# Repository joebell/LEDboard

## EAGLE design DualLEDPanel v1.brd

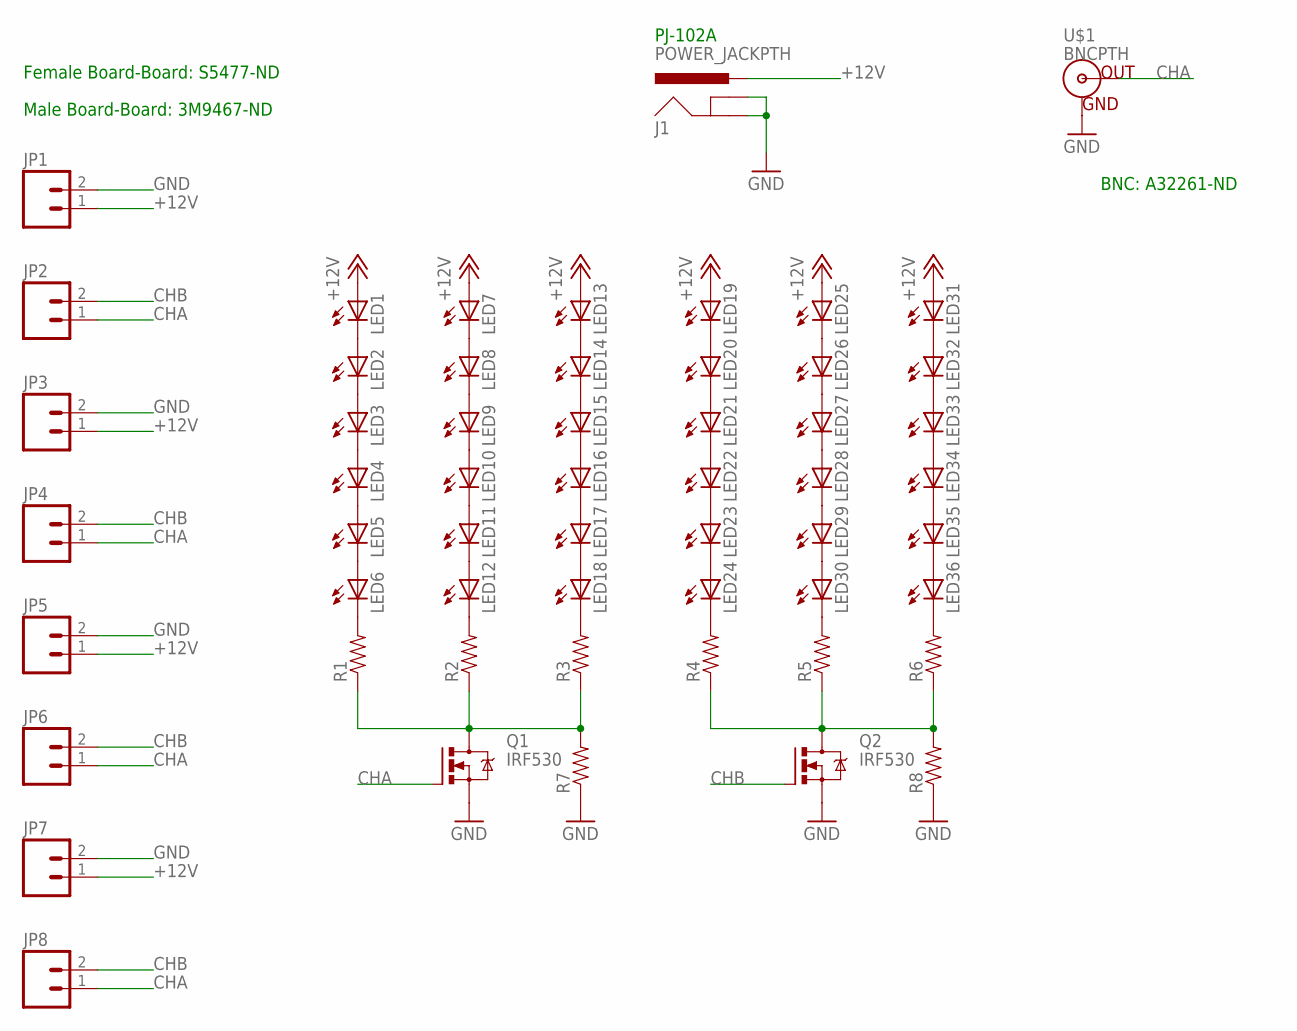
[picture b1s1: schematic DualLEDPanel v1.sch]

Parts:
J1: POWER_JACKPTH; POWER_JACK_PTH
JP1, JP2, JP3, JP4, JP5, JP6, JP7, JP8: M02PTH; 1X02
LED1, LED2, LED3, LED4, LED5, LED6, LED7, LED8, LED9, LED10, LED11, LED12, LED13, LED14, LED15, LED16, LED17, LED18, LED19, LED20, LED21, LED22, LED23, LED24, LED25, LED26, LED27, LED28, LED29, LED30, LED31, LED32, LED33, LED34, LED35, LED36: LED5MM
Q1, Q2: IRF530; TO220BV
R1, R2, R3, R4, R5, R6, R7, R8: RESISTORPTH-1/4W; AXIAL-0.4
U$1: BNCPTH; BNC

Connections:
+12V: J1.PWR, JP1.1, JP3.1, JP5.1, JP7.1, LED1.A, LED7.A, LED13.A, LED19.A, LED25.A, LED31.A
CHA: JP2.1, JP4.1, JP6.1, JP8.1, Q1.G, U$1.S (OUT)
CHB: JP2.2, JP4.2, JP6.2, JP8.2, Q2.G
GND: J1.GND, J1.GNDBREAK, JP1.2, JP3.2, JP5.2, JP7.2, Q1.S, Q2.S, R7.P$1 (1), R8.P$1 (1), U$1.GND
unnamed: LED1.K (C), LED2.A
unnamed: LED2.K (C), LED3.A
unnamed: LED3.K (C), LED4.A
unnamed: LED4.K (C), LED5.A
unnamed: LED5.K (C), LED6.A
unnamed: LED6.K (C), R1.P$2 (2)
unnamed: LED7.K (C), LED8.A
unnamed: LED8.K (C), LED9.A
unnamed: LED9.K (C), LED10.A
unnamed: LED10.K (C), LED11.A
unnamed: LED11.K (C), LED12.A
unnamed: LED12.K (C), R2.P$2 (2)
unnamed: LED13.K (C), LED14.A
unnamed: LED14.K (C), LED15.A
unnamed: LED15.K (C), LED16.A
unnamed: LED16.K (C), LED17.A
unnamed: LED17.K (C), LED18.A
unnamed: LED18.K (C), R3.P$2 (2)
unnamed: LED19.K (C), LED20.A
unnamed: LED20.K (C), LED21.A
unnamed: Q1.D, R1.P$1 (1), R2.P$1 (1), R3.P$1 (1), R7.P$2 (2)
unnamed: LED21.K (C), LED22.A
unnamed: LED22.K (C), LED23.A
unnamed: Q2.D, R4.P$1 (1), R5.P$1 (1), R6.P$1 (1), R8.P$2 (2)
unnamed: LED23.K (C), LED24.A
unnamed: LED24.K (C), R4.P$2 (2)
unnamed: LED25.K (C), LED26.A
unnamed: LED26.K (C), LED27.A
unnamed: LED27.K (C), LED28.A
unnamed: LED28.K (C), LED29.A
unnamed: LED29.K (C), LED30.A
unnamed: LED30.K (C), R5.P$2 (2)
unnamed: LED31.K (C), LED32.A
unnamed: LED32.K (C), LED33.A
unnamed: LED33.K (C), LED34.A
unnamed: LED34.K (C), LED35.A
unnamed: LED35.K (C), LED36.A
unnamed: LED36.K (C), R6.P$2 (2)

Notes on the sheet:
Female Board-Board: S5477-ND
Male Board-Board: 3M9467-ND
BNC: A32261-ND
PJ-102A

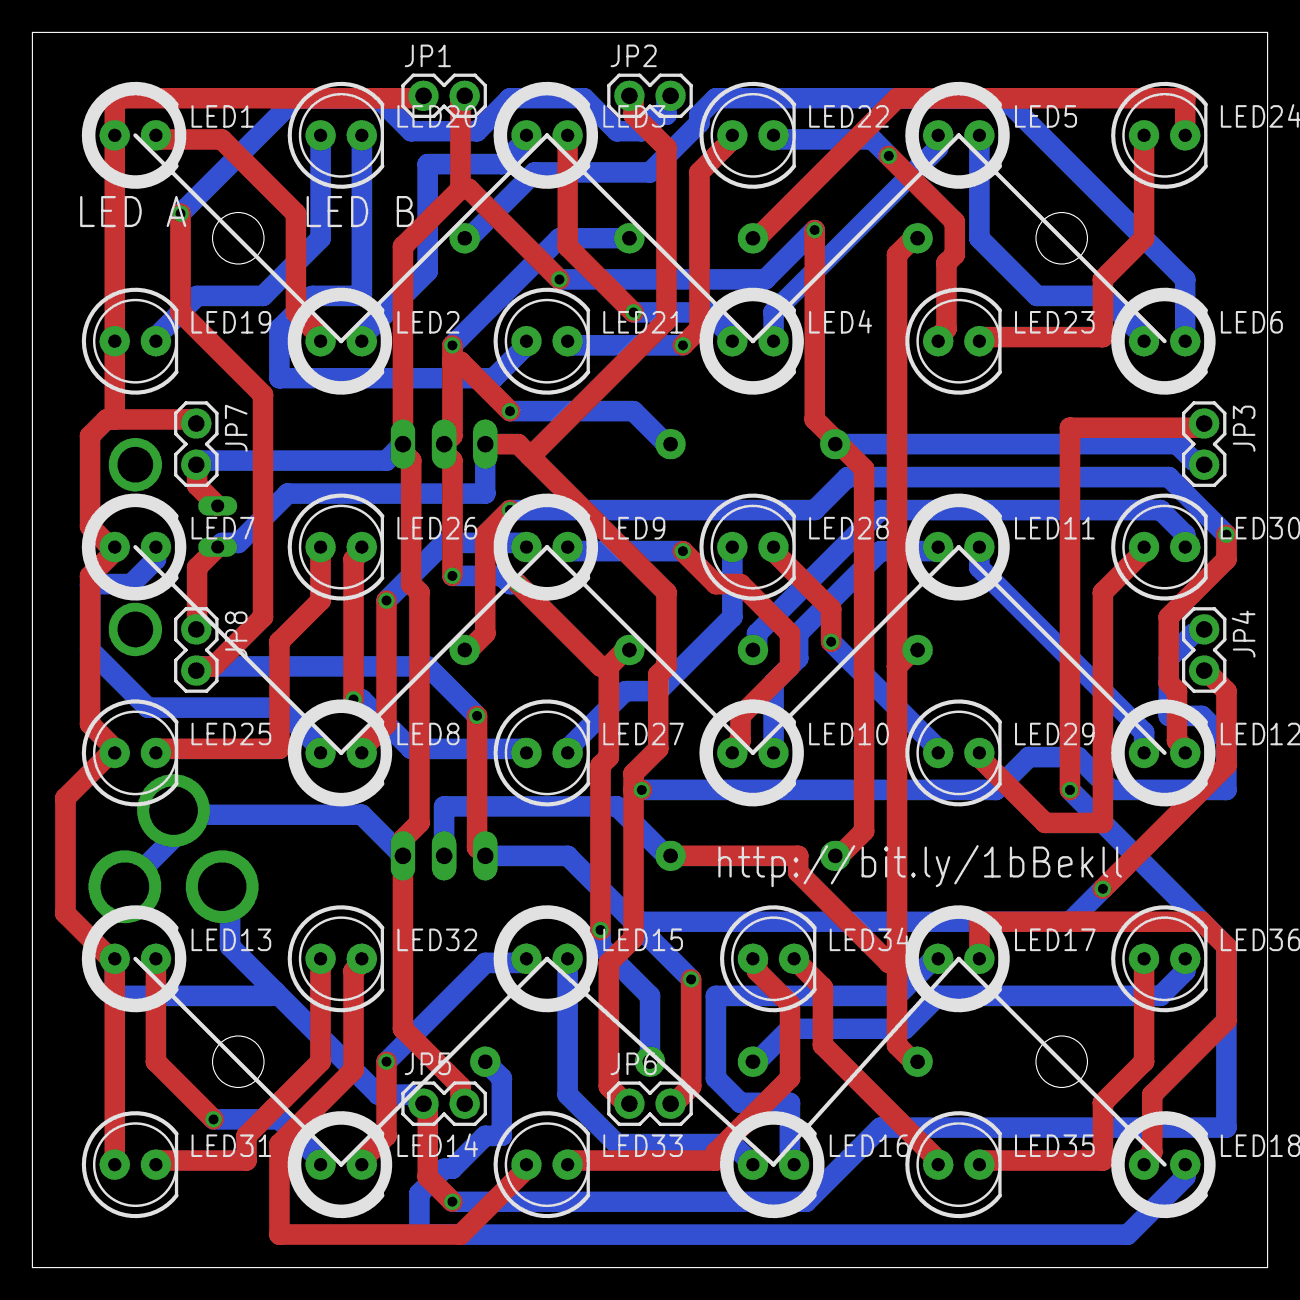
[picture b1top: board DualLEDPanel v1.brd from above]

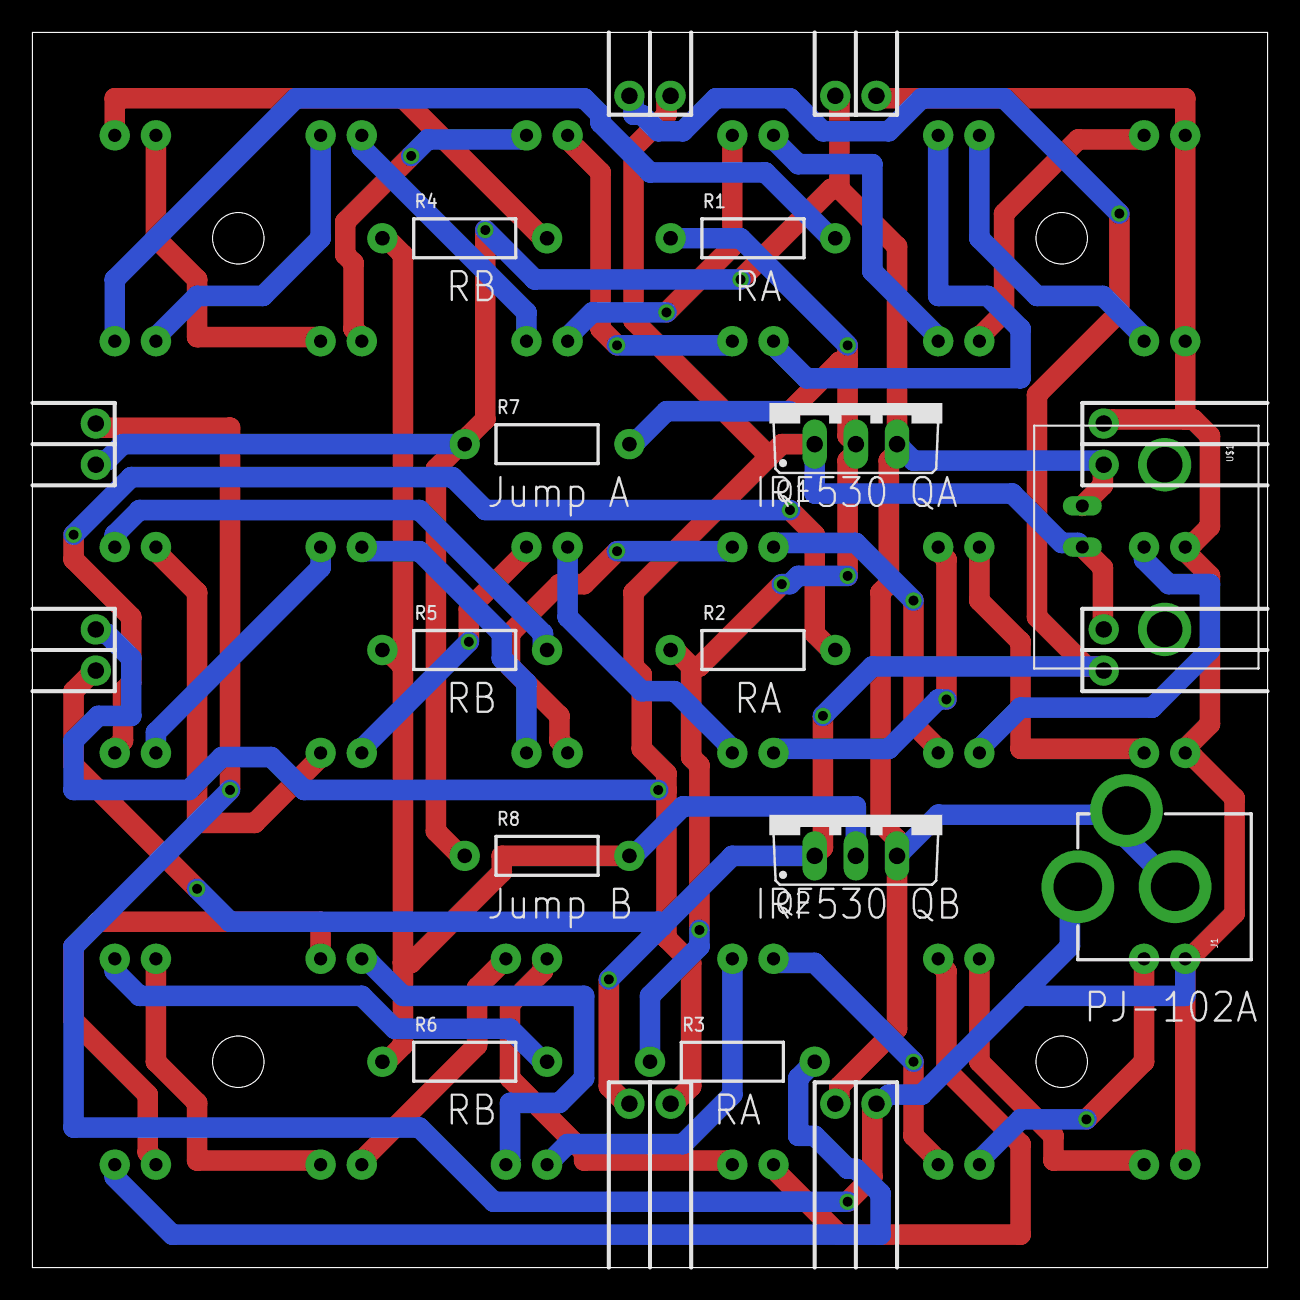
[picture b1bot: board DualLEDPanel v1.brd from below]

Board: 2 copper layers, 76.2 x 76.2 mm, 56 parts (12 on the bottom side), 42 nets.

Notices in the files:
parts and their libraries:
SparkFun-LED: Licensing: CC v3.0 Share-Alike You are welcome to use this library for commercial purposes.
